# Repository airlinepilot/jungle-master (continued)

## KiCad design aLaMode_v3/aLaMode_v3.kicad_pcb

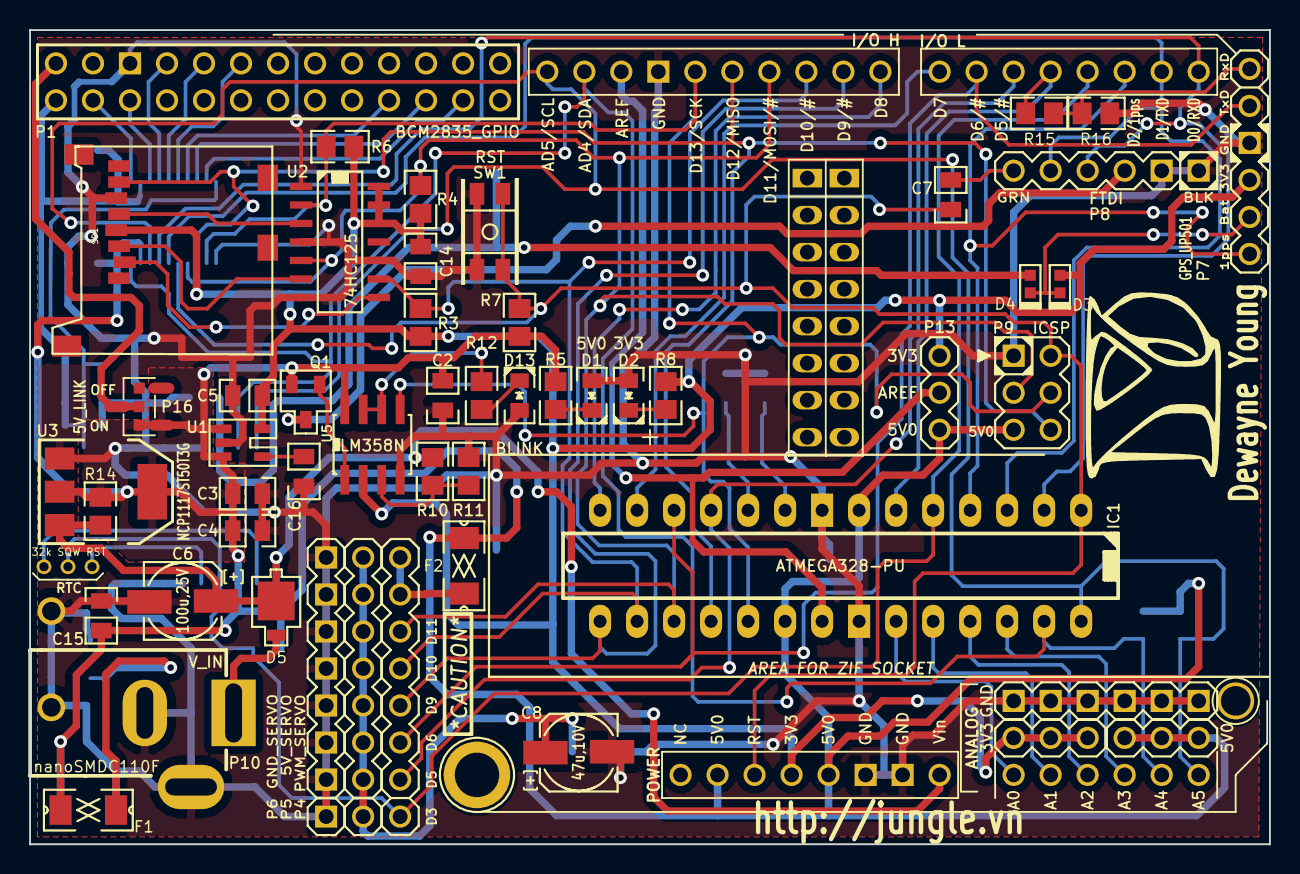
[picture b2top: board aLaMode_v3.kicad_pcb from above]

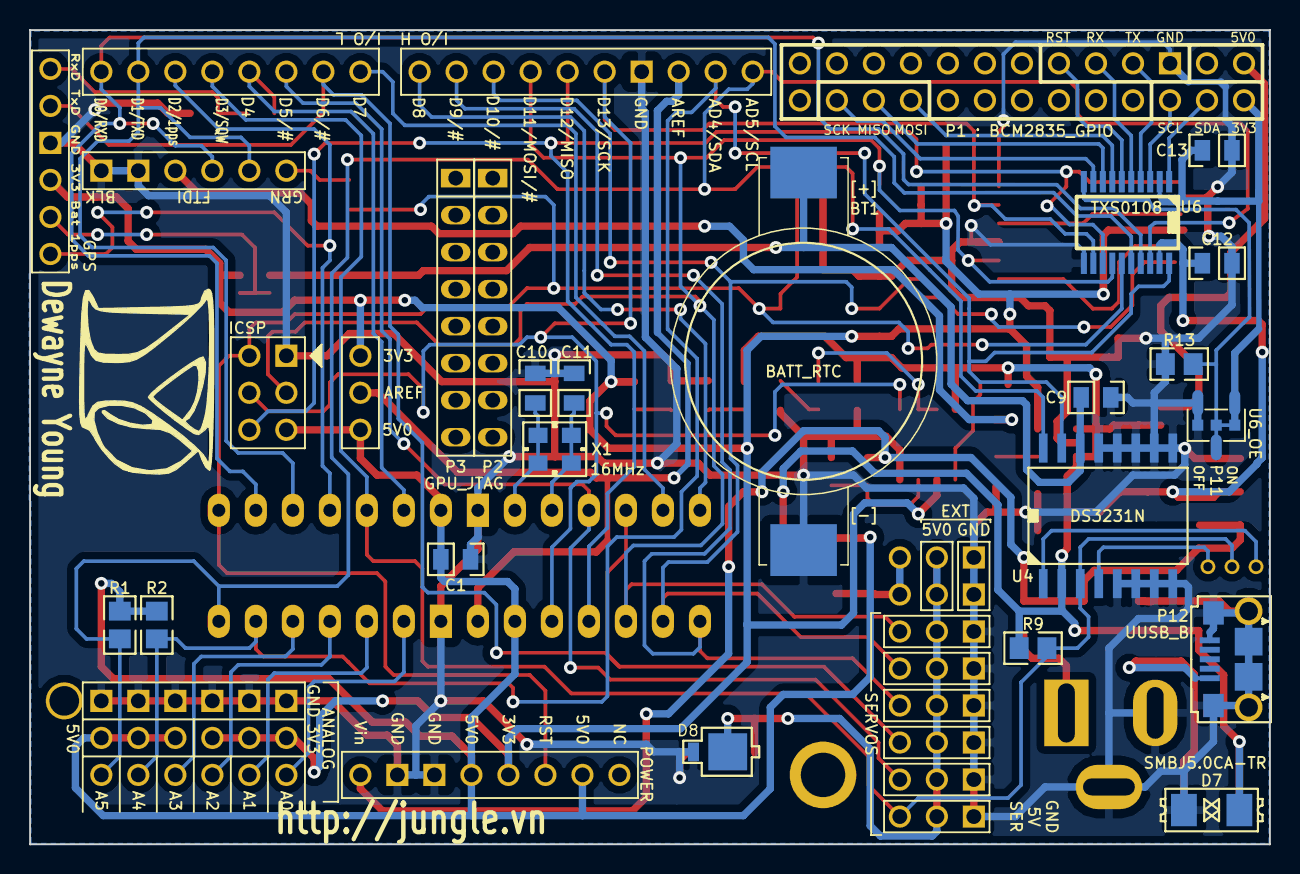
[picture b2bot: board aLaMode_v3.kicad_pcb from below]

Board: 2 copper layers, 85.1 x 55.9 mm, 76 parts (20 on the bottom side), 59 nets.

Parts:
B2, B3, B15: I/O; I%2fO
BT1: BATT_RTC; CR1632_2
C1, C2, C4, C7, C9, C12, C13, C14: 100n; c_0805
C3: 2u2 Tant; c_0805
C5: 2u2; c_0805
C6: 100u,25V; C_ELCO_SMD
C8: 47u,10V; C_ELCO_SMD
C10, C11: 22p; c_0805
C15: 1n; c_0805
C16: 10n; c_0805
D1: 5V0; led_0805
D2: 3V3; led_0805
D3, D4: RB886G; d_VMD2
D5, D8: MBRM110LT1G; do_457
D7: SMBJ5.0CA-TR; diode-DO214AA
D13: BLINK; led_0805
DIP1: DIP
F1, F2: nanoSMDC110F; f_1206
IC1: ATMEGA328-PU; DIP-28__300_ELL
P1: BCM2835_GPIO; Header_GPIO
P2: GPU_JTAG; Header_GPU_JTAG
P3: LAN_JTAG; Header_GPU_JTAG
P4: PWM_SERVO; Header_Servo
P5: 5V_SERVO; Header_Servo
P6: GND_SERVO; Header_Servo
P7: GPS_UP501; Header_GPS
P8: FTDI; Header_FTDI
P9: ICSP; Header_ICSP
P10: V_IN; JACK_ALIM
P11: U6_OE; Header_U6OE_SMT
P12: UUSB_B; USB_B_Micro
P13: AREF; Header_A_REF
P14: ANALOG_5V0; Header_6x1
P15: ANALOG_GND; Header_6x1
P16: 5V_LINK; Header_U6OE_SMT
PCB1: PCB
Q1: FDN340P; SOT23-3
R1, R2, R3, R4, R6, R7, R9, R10, R11, R13: 10k; r_0805
R5, R8: 1k5; r_0805
R12: 1k; r_0805
R14: 0E; r_0805
R15: 8k2; r_0805
R16: 16k; r_0805
SD1: SD_CARD_MICRO; MICROSD_tme
SHIELD1: ARDUINO_SHIELD; ARDUINO_SHIELD_2_040pins
SW1: RST; SW_SMD
U1: LP2985-33DBVR; SOT23-5
U2: 74HC125; SO14E
U3: NCP1117ST50T3G; SOT223
U4: DS3231N; DS3231
U5: LM358N; SO8E
U6: TXS0108; tssop-20
X1: 16MHz; Xtal_SMD2

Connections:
+3.3V: C5.1, C14.2, D3.1, P7.4, P13.1, P14.4, P14.5, P14.6, R3.1, R4.1, R6.1, R8.1, SD1.4, SHIELD1.3V3, U1.5, U2.12, U2.13, U2.14, U5.2
/5V_INT: F2.2, P4.7, P4.8
/5V_SERVO: C8.1, D8.2, P5.1, P5.2, P5.3, P5.4, P5.5, P5.6, P5.7, P5.8
/AREF: IC1.21, P13.2, SHIELD1.AREF
/GPS_BAT: D3.2, D4.2, P7.5
/GPS_Rx: P7.1, R15.2, R16.1
/PB0: IC1.14, SHIELD1.8
/PB1: IC1.15, P4.4, SHIELD1.9
/PB6: C10.1, IC1.9, X1.1
/PB7: C11.1, IC1.10, X1.2
/PC0: IC1.23, SHIELD1.AD0
/PC1: IC1.24, SHIELD1.AD1
/PC2: IC1.25, SHIELD1.AD2
/PC3: IC1.26, SHIELD1.AD3
/PD2_1pps: IC1.4, P7.6, SHIELD1.2
/PD4_GPS_Rx: IC1.6, R15.1, SHIELD1.4
/PD5: IC1.11, P4.2, SHIELD1.5
/PD6_GPS_Tx: IC1.12, P4.3, P7.2, SHIELD1.6
/PD7: IC1.13, SHIELD1.7
/RPi/5V0: C1.1, C2.1, C3.1, C4.1, C12.2, C15.1, D7.1, F1.2, F2.1, IC1.7, IC1.20, P9.2, P13.3, P14.1, P14.2, P14.3, P16.1, Q1.S, R1.1, R2.1, R5.1, R7.1, R9.1, R14.2, SHIELD1.5V, U1.1, U1.3, U3.2, U3.4, U4.2, U5.8, U6.19
/RPi/MISO: IC1.18, P9.1, SD1.7, SHIELD1.12, U6.13
/RPi/MOSI: IC1.17, P4.6, P9.4, R4.2, SHIELD1.11, U2.5, U6.14
/RPi/RESET: C7.2, IC1.1, P9.5, R7.2, SHIELD1.RST, SW1.2, U6.15
/RPi/RXD: IC1.2, P8.4, SHIELD1.0, U6.17
/RPi/Rpi_3V3: C13.2, P1.1, P11.1, P11.2, R13.1, U6.2, U6.10
/RPi/Rpi_5V0: P1.2, P16.2
/RPi/Rpi_MISO: P1.21, U6.8
/RPi/Rpi_MOSI: P1.19, U6.7
/RPi/Rpi_RST: P1.12, U6.6
/RPi/Rpi_Rx: P1.10, U6.5
/RPi/Rpi_SCK: P1.23, U6.9
/RPi/Rpi_SCL: P1.5, U6.3
/RPi/Rpi_SDA: P1.3, U6.1
/RPi/Rpi_Tx: P1.8, U6.4
/RPi/SCK: IC1.19, P9.3, R6.2, SHIELD1.13, U2.2, U5.5, U6.12
/RPi/SCL: IC1.28, R1.2, SHIELD1.AD5, U4.16, U6.18
/RPi/SDA: IC1.27, R2.2, SHIELD1.AD4, U4.15, U6.20
/RPi/TXD: IC1.3, P8.5, SHIELD1.1, U6.16
/SD_CLK: SD1.5, U2.3
/SD_CS: SD1.2, U2.8
/SD_DATA_IN: SD1.3, U2.6
/SS: IC1.16, P4.5, R3.2, SHIELD1.10, U2.9
/aLaMode_pwr/CMP: R10.2, R11.1, U5.3
/aLaMode_pwr/GATE_CMD: Q1.G, U5.1
/aLaMode_pwr/PWR_IN: D5.1, P10.1
/aLaMode_pwr/USBVCC: P8.3, Q1.D
/aLaMode_pwr/USB_IN: F1.1, P12.1
/aLaMode_pwr/V_IN: C6.1, D5.2, R10.1, R14.1, SHIELD1.V_IN, U3.3
/aLaMode_rtc/32k: B15.1, U4.1
/aLaMode_rtc/BAT: BT1.+, C9.1, D4.1, U4.14
/aLaMode_rtc/PD3_SQW: B2.1, IC1.5, P4.1, R9.2, SHIELD1.3, U4.3
/aLaMode_rtc/RST: B3.1, U4.4
/~RTS: C7.1, P8.6
GND: BT1.-, C1.2, C2.2, C3.2, C4.2, C5.2, C6.2, C8.2, C9.2, C10.2, C11.2, C12.1, C13.1, C14.1, C15.2, C16.2, D1.2, D2.2, D7.2, D8.1, D13.2, IC1.8, IC1.22, P1.6, P6.1, P6.2, P6.3, P6.4, P6.5, P6.6, P6.7, P6.8, P7.3, P8.1, P8.2, P9.6, P10.2, P10.3, P11.3, P12.5, P12.T1, P12.T2, P12.T3, P12.T4, P12.T5, P12.T6, P15.1, P15.2, P15.3, P15.4, P15.5, P15.6, R11.2, R13.2, R16.2, SD1.6, SHIELD1.GND1, SHIELD1.GND2, SHIELD1.GND3, SW1.1, U1.2, U2.1, U2.4, U2.7, U2.10, U3.1, U4.5, U4.6, U4.7, U4.8, U4.9, U4.10, U4.11, U4.12, U4.13, U5.4, U6.11
unnamed: C16.1, U1.4
unnamed: D1.1, R5.2
unnamed: D13.1, R12.2
unnamed: R12.1, U5.6, U5.7
unnamed: D2.1, R8.2

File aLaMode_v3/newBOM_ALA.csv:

"Id";"Designator";"Package";"Quantity";"Designation";"Supplier and ref";
1;"SD1";"MICROSD_tme";1;"SD_CARD_MICRO";;;
2;"G***,G***";"LOGO";2;"LOGO";;;
3;"P6";"Header_Servo";1;"GND_SERVO";;;
4;"P5";"Header_Servo";1;"5V_SERVO";;;
5;"C15";"c_0805";1;"1n";;;
6;"D7";"diode-DO214AA";1;"SMBJ5.0CA-TR";;;
7;"C16";"c_0805";1;"10n";;;
8;"D13";"led_0805";1;"BLINK";;;
9;"D2";"led_0805";1;"3V3";;;
10;"D1";"led_0805";1;"5V0";;;
11;"U6";"tssop-20";1;"TXS0108";;;
12;"R13,R6,R4,R3,R7,R1,R2,R9,R10,R11";"r_0805";10;"10k";;;
13;"C14,C13,C12,C7,C1,C4,C9,C2";"c_0805";8;"100n";;;
14;"U2";"SO14E";1;"74HC125";;;
15;"SW1";"SW_SMD";1;"RST";;;
16;"C11,C10";"c_0805";2;"22p";;;
17;"C5";"c_0805";1;"2u2";;;
18;"C3";"c_0805";1;"2u2 Tant";;;
19;"DIP1";"DIP";1;"DIP";;;
20;"R5,R8";"r_0805";2;"1k5";;;
21;"B3,B2,B15";"I%2fO";3;"I/O";;;
22;"X1";"Xtal_SMD2";1;"16MHz";;;
23;"U4";"DS3231";1;"DS3231N";;;
24;"R12";"r_0805";1;"1k";;;
25;"BT1";"CR1632_2";1;"BATT_RTC";;;
26;"U1";"SOT23-5";1;"LP2985-33DBVR";;;
27;"U3";"SOT223";1;"NCP1117ST50T3G";;;
28;"Q1";"SOT23-3";1;"FDN340P";;;
29;"U5";"SO8E";1;"LM358N";;;
30;"C8";"C_ELCO_SMD";1;"47u,10V";;;
31;"C6";"C_ELCO_SMD";1;"100u,25V";;;
32;"P4";"Header_Servo";1;"PWM_SERVO";;;
33;"P7";"Header_GPS";1;"GPS_UP501";;;
34;"P2";"Header_GPU_JTAG";1;"GPU_JTAG";;;
35;"P3";"Header_GPU_JTAG";1;"LAN_JTAG";;;
36;"P12";"USB_B_Micro";1;"UUSB_B";;;
37;"P9";"Header_ICSP";1;"ICSP";;;
38;"D3,D4";"d_VMD2";2;"RB886G";;;
39;"F1,F2";"f_1206";2;"nanoSMDC110F";;;
40;"D5,D8";"do_457";2;"MBRM110LT1G";;;
41;"P10";"JACK_ALIM";1;"V_IN";;;
42;"P1";"Header_GPIO";1;"BCM2835_GPIO";;;
43;"P13";"Header_A_REF";1;"AREF";;;
44;"P14";"Header_6x1";1;"ANALOG_5V0";;;
45;"P15";"Header_6x1";1;"ANALOG_GND";;;
46;"P11";"Header_U6OE_SMT";1;"U6_OE";;;
47;"P16";"Header_U6OE_SMT";1;"5V_LINK";;;
48;"PCB1";"PCB";1;"PCB";;;
49;"R14";"r_0805";1;"0E";;;
50;"P8";"Header_FTDI";1;"FTDI";;;
51;"SHIELD1";"ARDUINO_SHIELD_2_040pins";1;"ARDUINO_SHIELD";;;
52;"IC1";"DIP-28__300_ELL";1;"ATMEGA328-PU";;;
53;"R15";"r_0805";1;"8k2";;;
54;"R16";"r_0805";1;"16k";;;

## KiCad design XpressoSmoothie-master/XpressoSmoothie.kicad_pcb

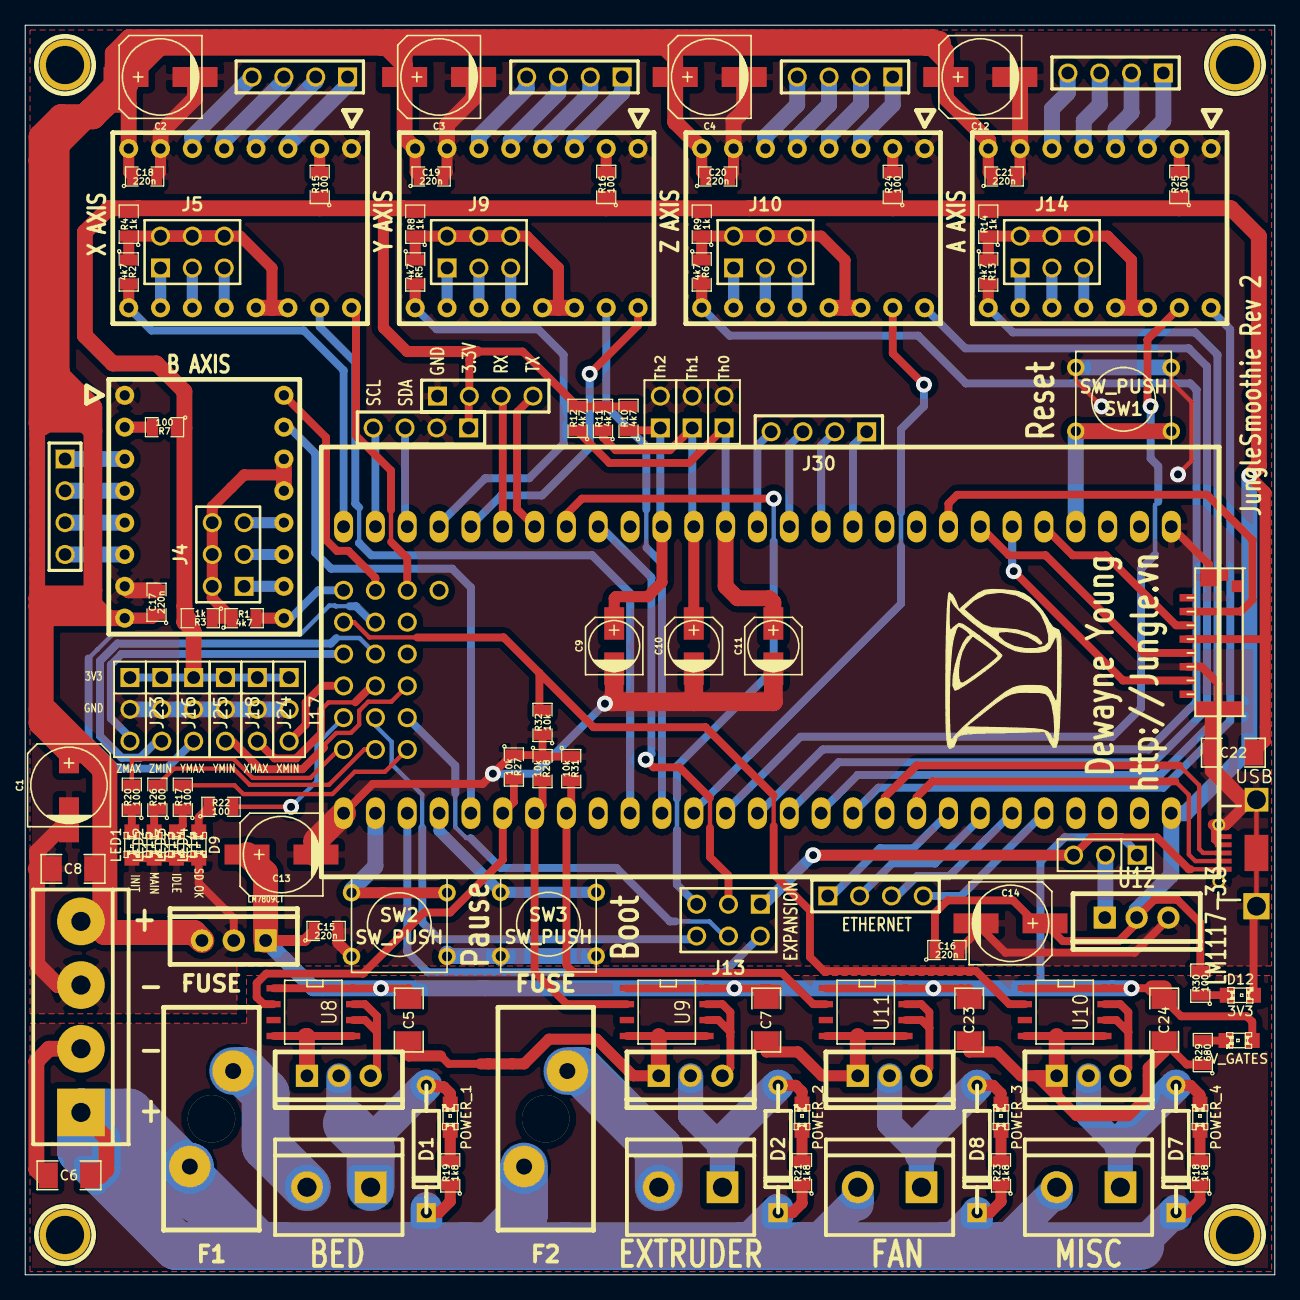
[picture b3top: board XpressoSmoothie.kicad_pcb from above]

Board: 2 copper layers, 99.7 x 99.7 mm, 127 parts (0 on the bottom side), 131 nets.

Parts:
C1, C2, C3, C4, C12, C13, C14: 100u; c_elec_6.3x7.7
C5, C6, C7, C8, C23, C24: 1u/50v; SM1206
C9, C10, C11: 10u; c_elec_4x5.3
C15, C16, C17, C18, C19, C20, C21: 220n; SM0805
C22: 1u; SM1206
D1, D2, D7, D8: 1N4007; DO-41
D3: POWER_1; LED-0805
D4: POWER_2; LED-0805
D5: POWER_3; LED-0805
D6: POWER_4; LED-0805
D9: LED4; LED-0805
D11: V_GATES; LED-0805
D12: 3V3; LED-0805
D13: LED2; LED-0805
D14: LED3; LED-0805
D15: LED1; LED-0805
F1, F2: FUSE; FUSE-MINI-AUTO
Hole1, Hole2, Hole3, Hole4: CONN_1; 1pin
J1, J2, J7, J8, J12, J15, J27, J29, J30: HEADER_4; PIN_ARRAY_4x1
J3, J16, J17, J18, J23, J24, J25: HEADER_3; PIN_ARRAY_3X1
J4, J5, J9, J10, J14: HEADER_3X2; pin_array_3x2
J6: LPCXPRESSO_1769_HEADER; LPCXPRESS0_1769
J11: Pwr_in; bornier4
J13: HEADER_6; pin_array_3x2
J19, J20, J21, J22: HEADER_2; bornier2
J26: USB; USB_MICRO_RMC_noedge
J28: MICROSD-MOLEX; microsd-molex-47309
Q1, Q2, Q3, Q4: IRLB 8743; TO220_VERT_C
R1, R2, R5, R6, R10, R11, R12, R13: 4k7; SM0805
R3, R4, R8, R9, R14: 1k; SM0805
R7, R15, R16, R17, R20, R22, R24, R25, R26, R30: 100; SM0805
R18, R19, R21, R23: 1k8; SM0805
R27, R28, R31, R32: 10k; SM0805
R29: 680; SM0805
SW1, SW2, SW3: SW_PUSH; SW_PUSH_SMALL
Th0, Th1, Th2: CONN_2; PIN_ARRAY_2X1
U1, U2, U3, U4, U5: POLOLU_A4988; POLOLU
U7: LM7809CT; TO220_VERT_1117
U8, U9, U10, U11: TC4422A; SO8N
U12: LM1117-3.3; TO220_VERT_1117

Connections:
*32_RD-: J6.32, J27.4
*33_RD+: J6.33, J27.3
*34_TD-: J6.34, J27.2
*35_TD+: J6.35, J27.1
*Bootloader: J6.51, SW3.1
*CS: J6.8, J28.2
*CS0: J6.14, J30.4
*LED1: J6.101, R20.2
*LED2: J6.102, R26.2
*LED3: J6.103, R17.2
*LED4: J6.104, R22.2
*MISO: J6.6, J28.7
*MISO0: J6.12, J30.2
*MOSI: J6.5, J28.3
*MOSI0: J6.11, J30.1
*PLAY/PAUSE: J6.53, SW2.1
*RESET: J6.4, SW1.1
*RX: J6.21, J29.4
*SCK: J6.7, J28.5
*SCK0: J6.13, J30.3
*SCL0: J6.26, J15.4
*SDA0: J6.25, J15.3
*THERM0: C11.1, J6.15, R12.1, Th0.1
*THERM1: C10.1, J6.16, R11.1, Th1.1
*THERM2: C9.1, J6.17, R10.1, Th2.1
*TX: J6.22, J29.3
*USB-D+: J6.37, J26.3
*USB-D-: J6.36, J26.2
+3.3VP: C14.1, C16.1, C22.1, J6.28, J15.1, J16.1, J17.1, J18.1, J23.1, J24.1, J25.1, J28.4, J29.2, R3.2, R4.2, R7.1, R8.2, R9.2, R10.2, R11.2, R12.2, R14.2, R15.1, R16.1, R24.1, R25.1, R30.2, U12.2
+5V: J3.3, J13.1, J26.1
A-DIR: J6.38, U5.16
A-EN: J6.39, R13.2, U5.9
A-STEP: J6.42, U5.15
B-DIR: J6.117, U1.16
B-EN: J6.116, R1.2, U1.9
B-STEP: J6.50, U1.15
BUZZ: J6.20, J13.5
CLICK: J6.19, J13.3
ENC_A: J6.105, J13.6
ENC_B: J6.106, J13.4
GND: C1.2, C2.2, C3.2, C4.2, C8.2, C9.2, C10.2, C11.2, C12.2, C13.2, C14.2, C15.2, C16.2, C17.2, C18.2, C19.2, C20.2, C21.2, C22.2, D9.2, D12.2, D13.2, D14.2, D15.2, J6.1, J6.54, J11.3, J15.2, J16.2, J17.2, J18.2, J23.2, J24.2, J25.2, J26.4, J26.5, J26.6, J28.6, J28.GND, J28.POL, J29.1, R27.1, R28.1, R31.1, R32.1, SW1.2, SW2.2, SW3.2, Th0.2, Th1.2, Th2.2, U1.1, U1.7, U2.1, U2.7, U3.1, U3.7, U4.1, U4.7, U5.1, U5.7, U7.2, U12.1
GNDPWR: C5.2, C6.2, C7.2, C23.2, C24.2, J11.2, Q1.S, Q2.S, Q3.S, Q4.S, R29.1, U8.4, U8.5, U9.4, U9.5, U10.4, U10.5, U11.4, U11.5
unnamed: J10.5, U4.12
unnamed: J10.1, U4.10
unnamed: J8.4, U4.6
unnamed: J8.1, U4.3
unnamed: J8.2, U4.4
unnamed: J8.3, U4.5
unnamed: J10.3, U4.11
unnamed: J14.2, J14.4, J14.6, R13.1, R14.1, U5.13, U5.14
unnamed: J10.2, J10.4, J10.6, R6.1, R9.1, U4.13, U4.14
unnamed: J14.5, U5.12
unnamed: J14.1, U5.10
unnamed: J12.4, U5.6
unnamed: J12.1, U5.3
unnamed: J12.2, U5.4
unnamed: J12.3, U5.5
unnamed: J14.3, U5.11
unnamed: D2.1, D4.2, J20.1, Q2.D
unnamed: Q2.G, U9.6, U9.7
unnamed: D4.1, R21.2
unnamed: J5.2, J5.4, J5.6, R2.1, R4.1, U2.13, U2.14
unnamed: D1.1, D3.2, J19.1, Q1.D
unnamed: Q1.G, U8.6, U8.7
unnamed: D3.1, R19.2
unnamed: J9.5, U3.12
unnamed: J9.1, U3.10
unnamed: J7.4, U3.6
unnamed: J7.1, U3.3
unnamed: J7.2, U3.4
unnamed: J7.3, U3.5
unnamed: J9.3, U3.11
unnamed: J9.2, J9.4, J9.6, R5.1, R8.1, U3.13, U3.14
unnamed: J5.5, U2.12
unnamed: J5.1, U2.10
unnamed: J2.4, U2.6
unnamed: J2.1, U2.3
unnamed: J2.2, U2.4
unnamed: J2.3, U2.5
unnamed: J5.3, U2.11
unnamed: D9.1, R22.1
unnamed: D14.1, R17.1
unnamed: D13.1, R26.1
unnamed: D15.1, R20.1
unnamed: J3.2, U12.3
unnamed: F1.2, J19.2
unnamed: F2.2, J20.2
unnamed: D11.2, R29.2
unnamed: D6.2, D7.1, J22.1, Q4.D
unnamed: Q4.G, U10.6, U10.7
unnamed: D6.1, R18.2
unnamed: D5.2, D8.1, J21.1, Q3.D
unnamed: Q3.G, U11.6, U11.7
unnamed: D5.1, R23.2
unnamed: D12.1, R30.1
unnamed: J4.5, U1.12
unnamed: J4.1, U1.10
unnamed: J1.4, U1.6
unnamed: J1.1, U1.3
unnamed: J1.2, U1.4
unnamed: J1.3, U1.5
unnamed: J4.3, U1.11
unnamed: J4.2, J4.4, J4.6, R1.1, R3.1, U1.13, U1.14
unnamed: R15.2, U2.2
unnamed: R16.2, U3.2
unnamed: R24.2, U4.2
unnamed: R25.2, U5.2
unnamed: R7.2, U1.2
PANEL_KILL: J6.52, J13.2
POWER1: J6.49, R27.2, U8.2
POWER2: J6.48, R28.2, U9.2
POWER3: J6.47, R31.2, U11.2
POWER4: J6.113, R32.2, U10.2
Vgates: C5.1, C7.1, C13.1, C15.1, C23.1, C24.1, D11.1, J3.1, U7.3, U8.1, U8.8, U9.1, U9.8, U10.1, U10.8, U11.1, U11.8
Vin_Hi_curr: C6.1, D1.2, D2.2, D7.2, D8.2, F1.1, F2.1, J11.1, J21.2, J22.2, R18.1, R19.1, R21.1, R23.1
Vin_rmot: C1.1, C2.1, C3.1, C4.1, C8.1, C12.1, C17.1, C18.1, C19.1, C20.1, C21.1, J11.4, U1.8, U2.8, U3.8, U4.8, U5.8, U7.1
X-DIR: J6.118, U2.16
X-EN: J6.27, R2.2, U2.9
X-STEP: J6.45, U2.15
XMAX: J6.108, J24.3
XMIN: J6.107, J17.3
Y-DIR: J6.23, U3.16
Y-EN: J6.24, R5.2, U3.9
Y-STEP: J6.44, U3.15
YMAX: J6.114, J25.3
YMIN: J6.109, J18.3
Z-DIR: J6.40, U4.16
Z-EN: J6.41, R6.2, U4.9
Z-STEP: J6.43, U4.15
ZMAX: J6.110, J23.3
ZMIN: J6.111, J16.3

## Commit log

2016-06-23 LinuxCNC + BBB
    Jungle BBB Cape 6-Axis, 4Ch A/D
2016-06-23 Readme
    Added Readme file
2016-06-23 Ready Update
    Need to add LinuxCNC Debug
2016-06-24 Jungle-Notes
    MQTT - Failed to start after server restart
2016-06-24 AlaMode-V3.0
    3DPrinter cape
